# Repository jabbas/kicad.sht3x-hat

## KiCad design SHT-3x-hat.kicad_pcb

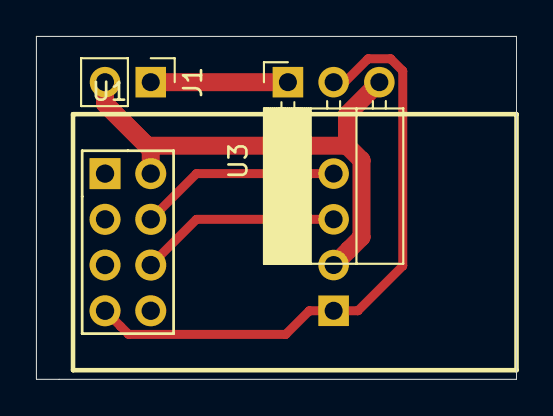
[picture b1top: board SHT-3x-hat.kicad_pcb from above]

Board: 2 copper layers, 26.7 x 19.1 mm, 4 parts (1 on the bottom side), 5 nets.

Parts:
J1: Power; PinHeader_1x02_P2.54mm_Vertical
U1: ESP-01
U2: SHT31; SHT3x-BOARD
U3: AMS1117-3.3; PinSocket_1x03_P2.54mm_Horizontal

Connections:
+5V: J1.1, U3.3
GND: J1.2, U1.2, U2.8, U3.1
unnamed: U1.4, U2.1
unnamed: U1.6, U2.4
unnamed: U1.7, U2.5, U3.2

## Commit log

2019-09-10 added edge cuts
2019-09-10 updated gitignore
